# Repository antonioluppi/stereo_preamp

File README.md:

# stereo_preamp
a mic to line level pre-amplifier working on a 9V single rail power supply

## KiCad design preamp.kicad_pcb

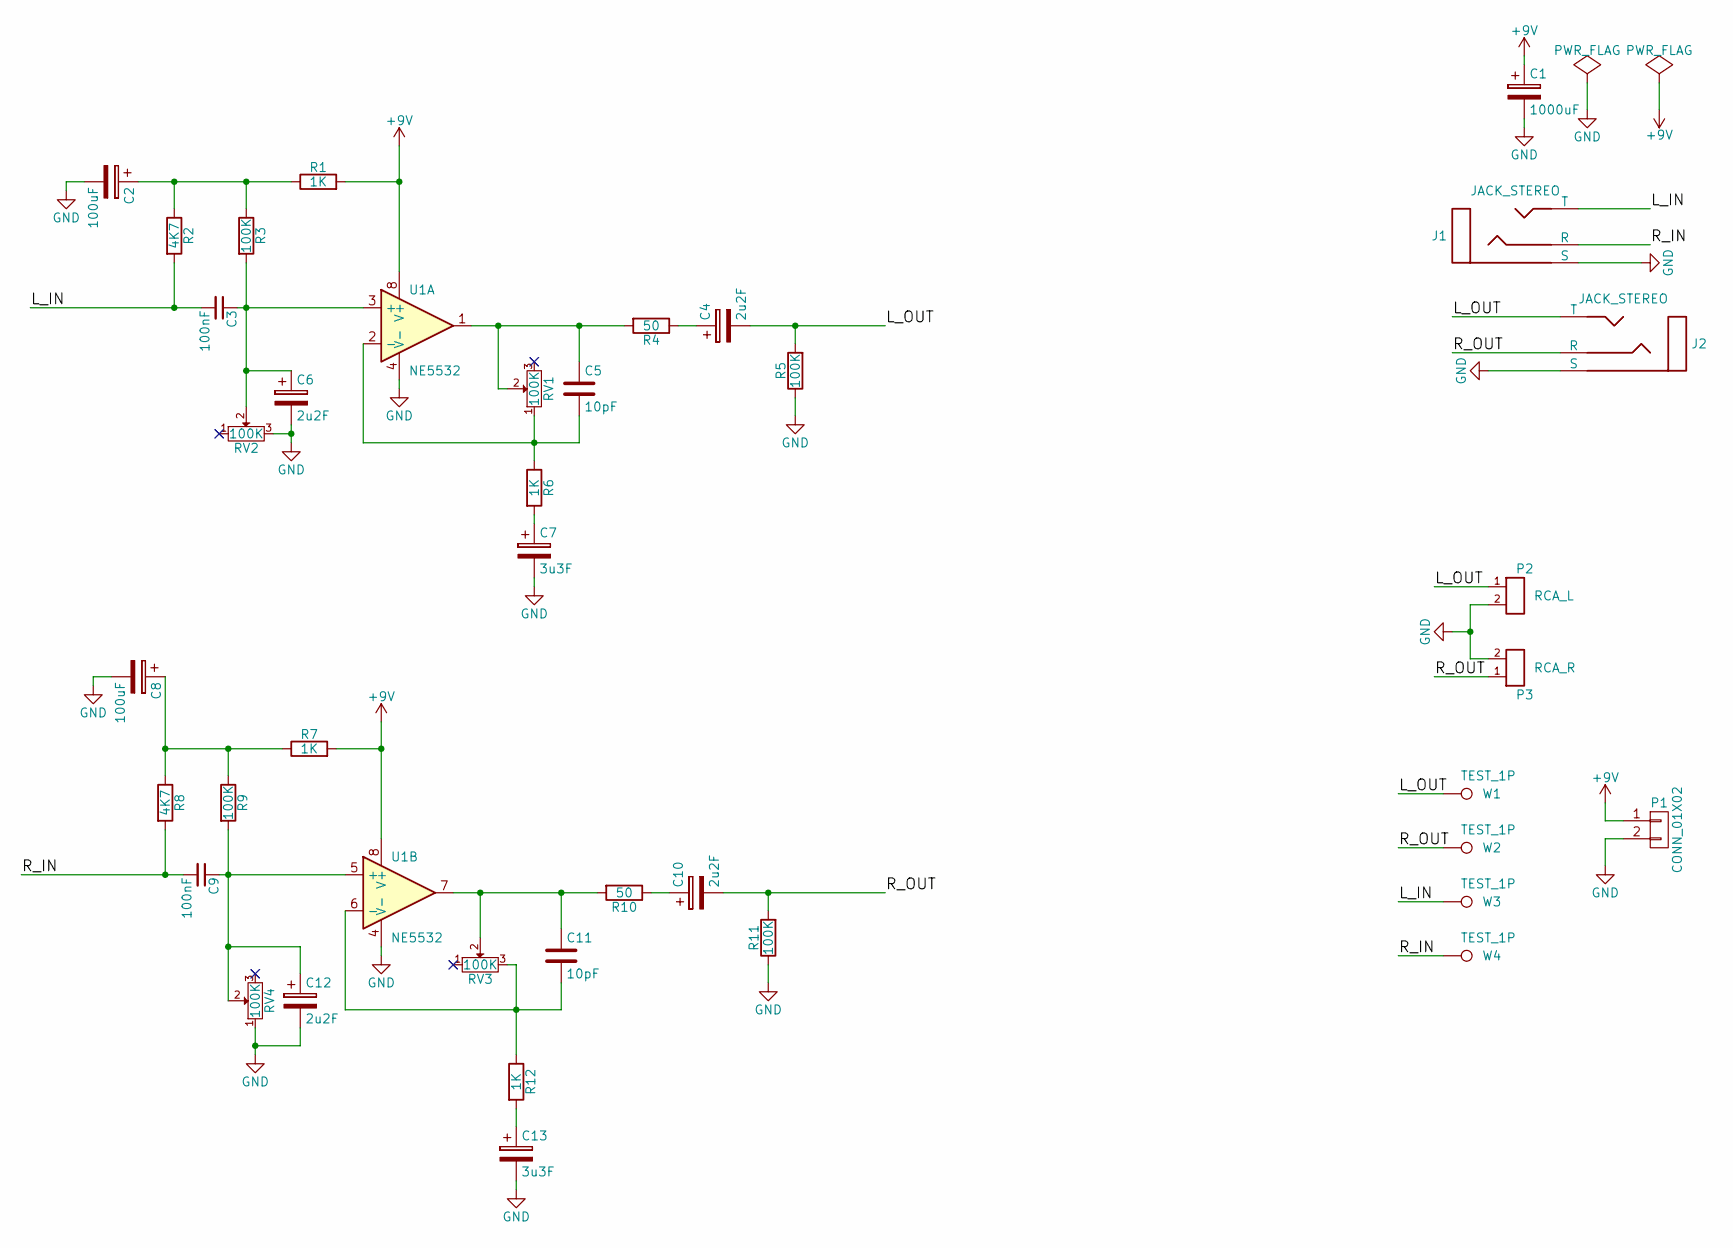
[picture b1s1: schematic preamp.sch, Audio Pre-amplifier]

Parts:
C1: 1000uF; C_Radial_D10_L20_P5
C2, C8: 100uF; C_Radial_D6.3_L11.2_P2.5
C3, C9: 100nF; C_Disc_D12_P7.75
C4, C6, C10, C12: 2u2F; C_Radial_D5_L11_P2.5
C5, C11: 10pF; C_Disc_D6_P5
C7, C13: 3u3F; C_Radial_D5_L11_P2.5
J1, J2: JACK_STEREO; audio_jack
P1: CONN_01X02; Pin_Header_Straight_1x02
P2: RCA_L; rca_white
P3: RCA_R; rca_red
R1, R6, R7, R12: 1K; Resistor_Horizontal_RM10mm
R2, R8: 4K7; Resistor_Horizontal_RM10mm
R3, R5, R9, R11: 100K; Resistor_Horizontal_RM10mm
R4, R10: 50; Resistor_Horizontal_RM10mm
RV1, RV2, RV3, RV4: 100K; Potentiometer_WirePads
U1: NE5532; DIP-8_W7.62mm
W1, W2, W3, W4: TEST_1P; Measurement_Point_Round-SMD-Pad_Big

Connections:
+9V: C1.1, P1.1, R1.2, R7.2, U1.8 (V+)
/L_IN: C3.2, J1.T, R2.2, W3.1
/L_OUT: C4.2, J2.T, P2.1, R5.2, W1.1
/R_IN: C9.2, J1.R, R8.2, W4.1
/R_OUT: C10.2, J2.R, P3.1, R11.2, W2.1
GND: C1.2, C2.2, C6.2, C7.2, C8.2, C12.2, C13.2, J1.S, J2.S, P1.2, P2.2, P3.2, R5.1, R11.1, RV2.3, RV4.1, U1.4 (V-)
unnamed: C2.1, R1.1, R2.1, R3.1
unnamed: C3.1, C6.1, R3.2, RV2.2, U1.3 (+)
unnamed: C4.1, R4.1
unnamed: C5.1, R4.2, RV1.2, U1.1
unnamed: C5.2, R6.1, RV1.1, U1.2 (-)
unnamed: C7.1, R6.2
unnamed: C8.1, R7.1, R8.1, R9.1
unnamed: C10.1, R10.1
unnamed: C11.1, R10.2, RV3.2, U1.7
unnamed: C11.2, R12.1, RV3.3, U1.6 (-)
unnamed: C9.1, C12.1, R9.2, RV4.2, U1.5 (+)
unnamed: C13.1, R12.2

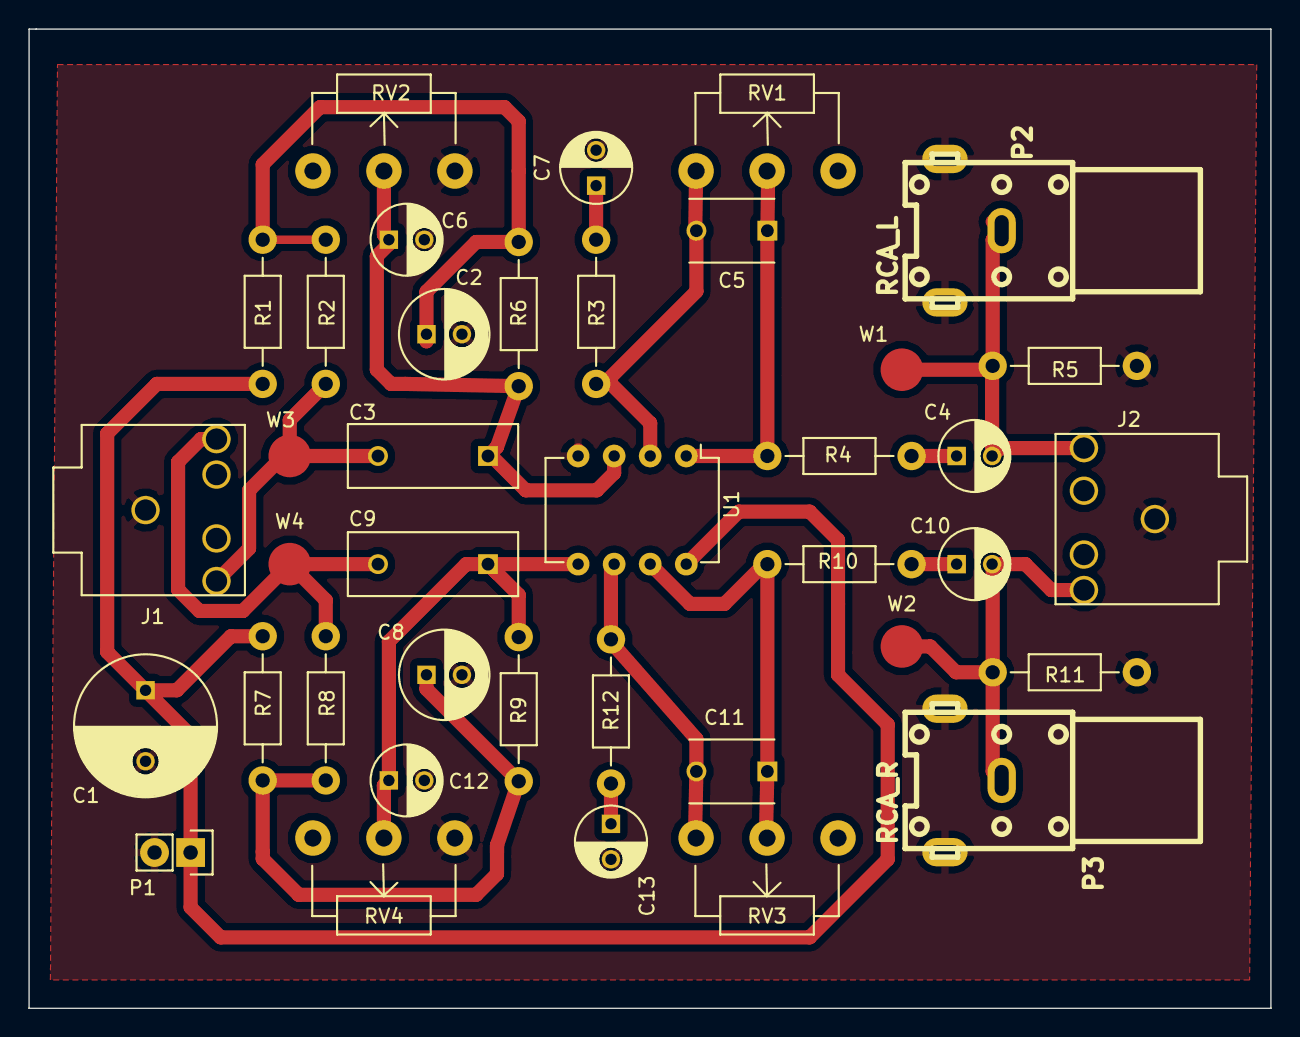
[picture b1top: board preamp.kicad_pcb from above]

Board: 2 copper layers, 87.5 x 69.0 mm, 39 parts (0 on the bottom side), 18 nets.

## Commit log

2016-10-03 primeiro esquemático
2016-10-05 Esquemático e netlist gerados
2016-10-07 mais layout
2016-10-13 pcb roteada
2017-07-25 nem sei
